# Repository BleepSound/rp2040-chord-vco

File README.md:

[![CC BY-SA 4.0][cc-by-sa-shield]][cc-by-sa]

# RP2040 VCO (Clone, made by Hagiwo)

Latest documentation available at https://bleepsound.github.io/modules/
VCO clone, originally made by HAGIWO ([link](https://note.com/solder_state/n/n64b91a171218) in japanese)

This work is licensed under a
[Creative Commons Attribution-ShareAlike 4.0 International License][cc-by-sa].

[![CC BY-SA 4.0][cc-by-sa-image]][cc-by-sa]

[cc-by-sa]: http://creativecommons.org/licenses/by-sa/4.0/
[cc-by-sa-image]: https://licensebuttons.net/l/by-sa/4.0/88x31.png
[cc-by-sa-shield]: https://img.shields.io/badge/License-CC%20BY--SA%204.0-lightgrey.svg

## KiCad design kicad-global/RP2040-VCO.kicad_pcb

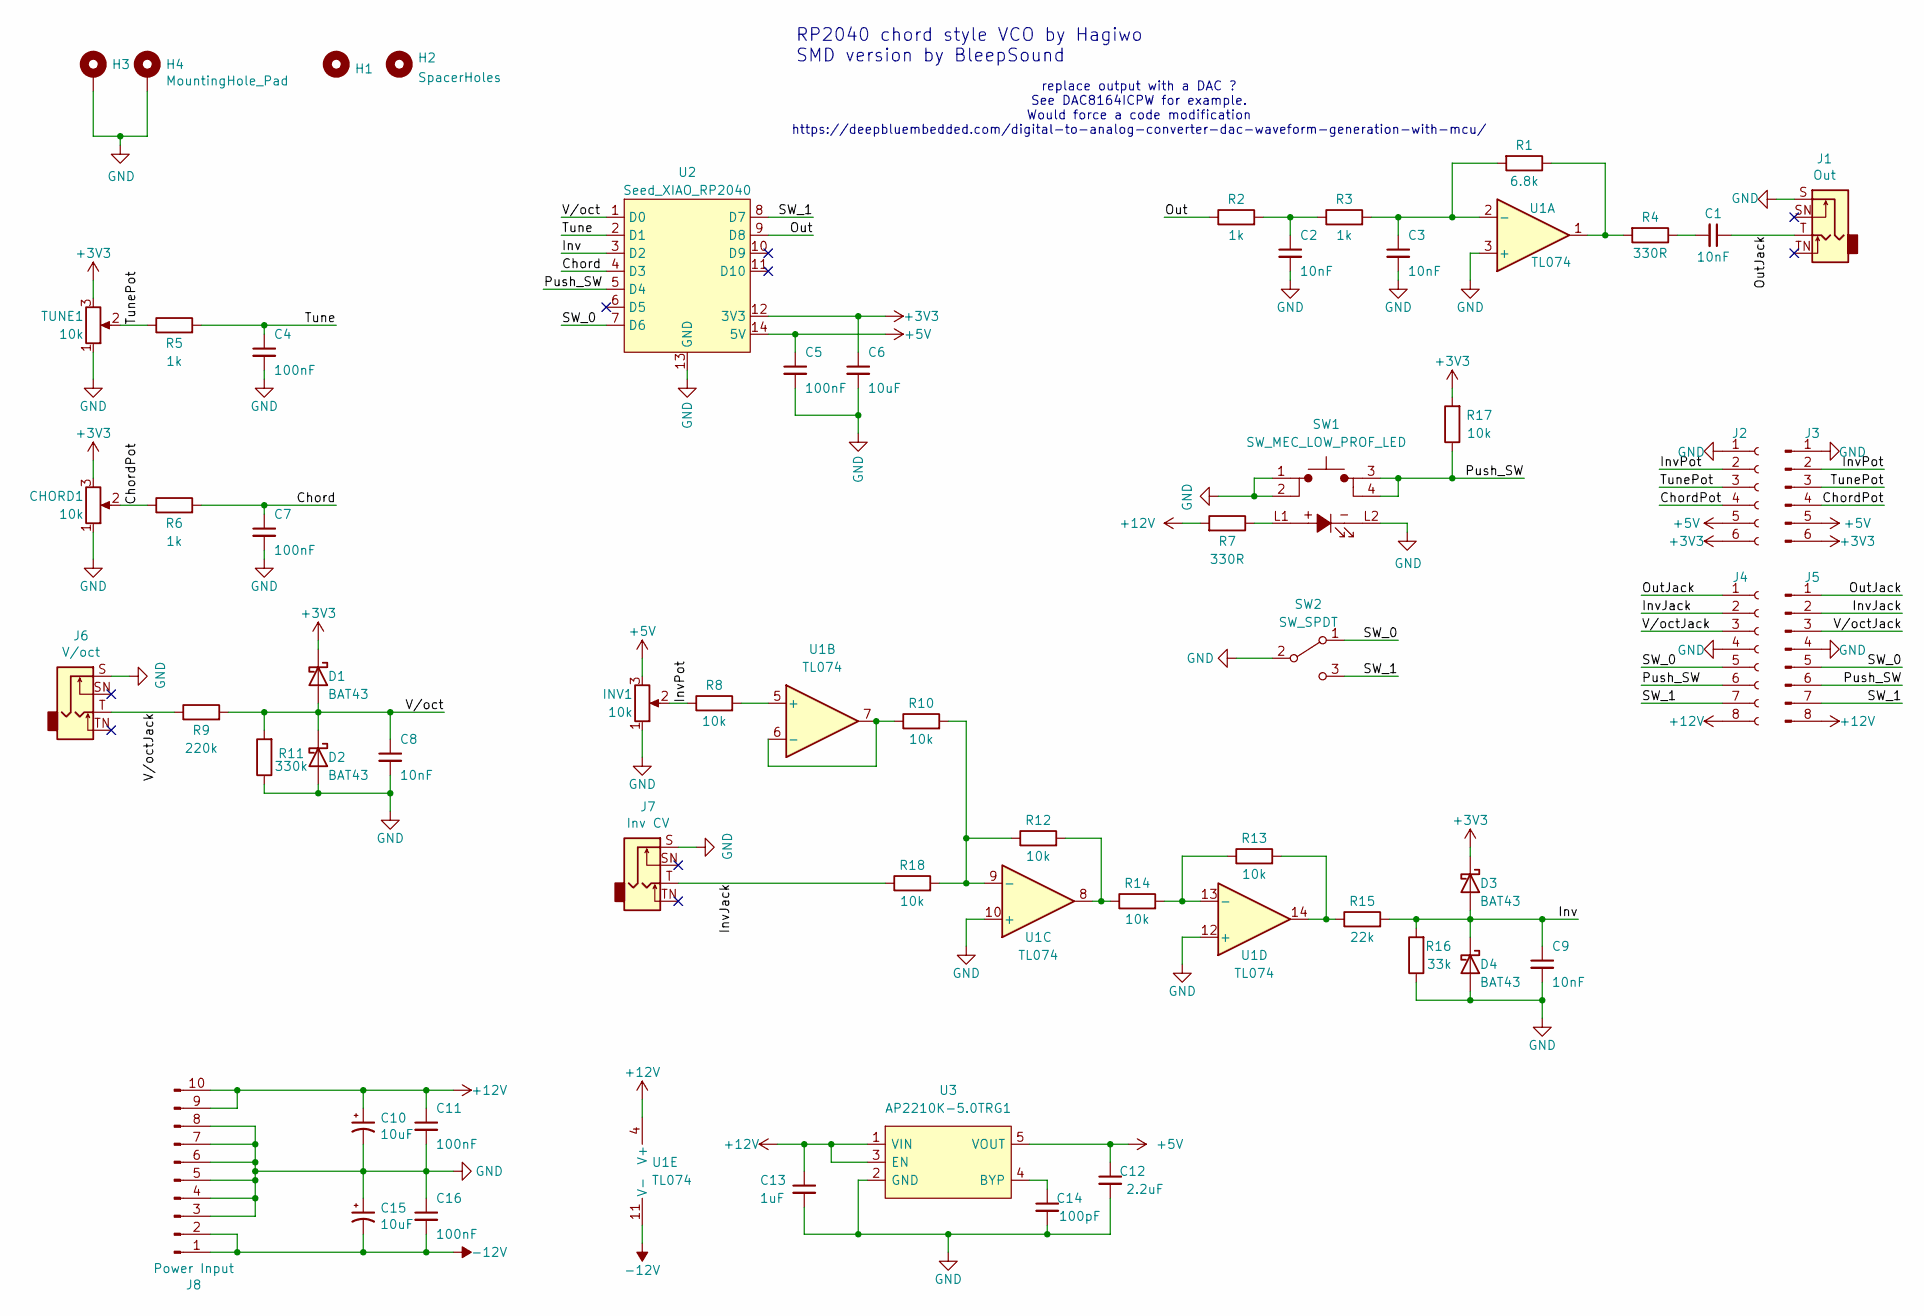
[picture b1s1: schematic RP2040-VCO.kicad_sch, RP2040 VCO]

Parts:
C1, C2, C3, C8, C9: 10nF; C_0805_2012Metric_Pad1.18x1.45mm_HandSolder
C4, C5, C7, C11, C16: 100nF; C_0805_2012Metric_Pad1.18x1.45mm_HandSolder
C6: 10uF; C_0805_2012Metric_Pad1.18x1.45mm_HandSolder
C10, C15: 10uF; CP_Elec_4x5.4
C12: 2.2uF; C_0805_2012Metric_Pad1.18x1.45mm_HandSolder
C13: 1uF; C_0805_2012Metric_Pad1.18x1.45mm_HandSolder
C14: 100pF; C_0805_2012Metric_Pad1.18x1.45mm_HandSolder
CHORD1: 10k; Pot-bourns-alpha
D1, D2, D3, D4: BAT43; D_SOD-123
H1, H2: SpacerHoles; MountingHole_3.2mm_M3
H3, H4: MountingHole_Pad; Doepfer Mounting hole
INV1: 10k; Pot-bourns-alpha
J1: Out; Thonkiconn
J2: Conn_01x06_Female; PinSocket_1x06_P2.54mm_Vertical
J3: Conn_01x06_Male; PinHeader_1x06_P2.54mm_Vertical
J4: Conn_01x08_Female; PinSocket_1x08_P2.54mm_Vertical
J5: Conn_01x08_Male; PinHeader_1x08_P2.54mm_Vertical
J6: V/oct; Thonkiconn
J7: Inv CV; Thonkiconn
J8: Power Input; IDC-Header_2x05_P2.54mm_Vertical
R1: 6.8k; R_0805_2012Metric_Pad1.20x1.40mm_HandSolder
R2, R3, R5, R6: 1k; R_0805_2012Metric_Pad1.20x1.40mm_HandSolder
R4, R7: 330R; R_0805_2012Metric_Pad1.20x1.40mm_HandSolder
R8, R10, R12, R13, R14, R17, R18: 10k; R_0805_2012Metric_Pad1.20x1.40mm_HandSolder
R9: 220k; R_0805_2012Metric_Pad1.20x1.40mm_HandSolder
R11: 330k; R_0805_2012Metric_Pad1.20x1.40mm_HandSolder
R15: 22k; R_0805_2012Metric_Pad1.20x1.40mm_HandSolder
R16: 33k; R_0805_2012Metric_Pad1.20x1.40mm_HandSolder
SW1: SW_MEC_LOW_PROF_LED; PB01-109TL
SW2: SW_SPDT; SW_Toggle_Blue_wSlots
TUNE1: 10k; Pot-bourns-alpha
U1: TL074; SOIC-14_3.9x8.7mm_P1.27mm
U2: Seed_XIAO_RP2040; Seed XIAO RP2040
U3: AP2210K-5.0TRG1; SOT95P282X130-5N

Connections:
+3V3: C6.1, CHORD1.3, D1.1 (K), D3.1 (K), J2.6, J3.6, R17.2, TUNE1.3, U2.12 (3V3)
+5V: C5.1, C12.1, INV1.3, J2.5, J3.5, U2.14 (5V), U3.5 (VOUT)
+12V: C10.1, C11.1, C13.1, J4.8, J5.8, J8.9, J8.10, R7.2, U1.4 (V+), U3.1 (VIN), U3.3 (EN)
-12V: C15.2, C16.2, J8.1, J8.2, U1.11 (V-)
/Chord: C7.1, R6.2, U2.4 (D3)
/ChordPot: CHORD1.2, J2.4, J3.4, R6.1
/Inv: C9.1, D3.2 (A), D4.1 (K), R15.2, R16.2, U2.3 (D2)
/InvJack: J4.2, J5.2, J7.T, R18.1
/InvPot: INV1.2, J2.2, J3.2, R8.1
/Out: R2.1, U2.9 (D8)
/OutJack: C1.1, J1.T, J4.1, J5.1
/Push_SW: J4.6, J5.6, R17.1, SW1.3, SW1.4, U2.5 (D4)
/SW_0: J4.5, J5.5, SW2.1 (A), U2.7 (D6)
/SW_1: J4.7, J5.7, SW2.3 (C), U2.8 (D7)
/Tune: C4.1, R5.2, U2.2 (D1)
/TunePot: J2.3, J3.3, R5.1, TUNE1.2
/V/oct: C8.1, D1.2 (A), D2.1 (K), R9.2, R11.2, U2.1 (D0)
/V/octJack: J4.3, J5.3, J6.T, R9.1
GND: C2.2, C3.2, C4.2, C5.2, C6.2, C7.2, C8.2, C9.2, C10.2, C11.2, C12.2, C13.2, C14.2, C15.1, C16.1, CHORD1.1, D2.2 (A), D4.2 (A), H3.1, H4.1, INV1.1, J1.S, J2.1, J3.1, J4.4, J5.4, J6.S, J7.S, J8.3, J8.4, J8.5, J8.6, J8.7, J8.8, R11.1, R16.1, SW1.1, SW1.2, SW1.L2, SW2.2 (B), TUNE1.1, U1.3 (+), U1.10 (+), U1.12 (+), U2.13 (GND), U3.2 (GND)
unnamed: C1.2, R4.1
unnamed: C2.1, R2.2, R3.1
unnamed: R1.1, R4.2, U1.1
unnamed: R7.1, SW1.L1
unnamed: R12.2, R14.1, U1.8
unnamed: R13.2, R15.1, U1.14
unnamed: C3.1, R1.2, R3.2, U1.2 (-)
unnamed: R8.2, U1.5 (+)
unnamed: R10.1, U1.6 (-), U1.7
unnamed: R10.2, R12.1, R18.2, U1.9 (-)
unnamed: R13.1, R14.2, U1.13 (-)
unnamed: C14.1, U3.4 (BYP)

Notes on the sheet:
replace output with a DAC ? See DAC8164ICPW for example. Would force a code modification https://deepbluembedded.com/digital-to-analog-converter-dac-waveform-generation-with-mcu/
RP2040 chord style VCO by Hagiwo SMD version by BleepSound

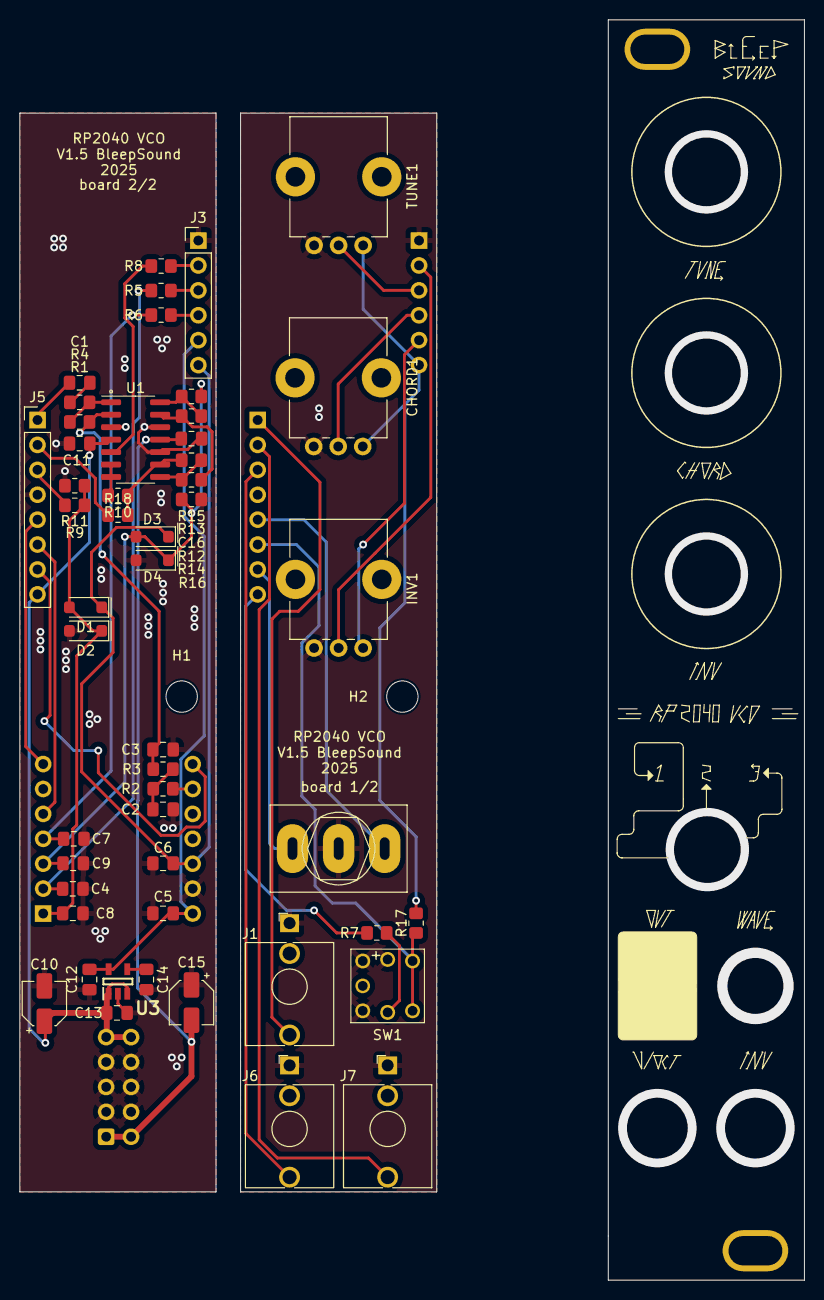
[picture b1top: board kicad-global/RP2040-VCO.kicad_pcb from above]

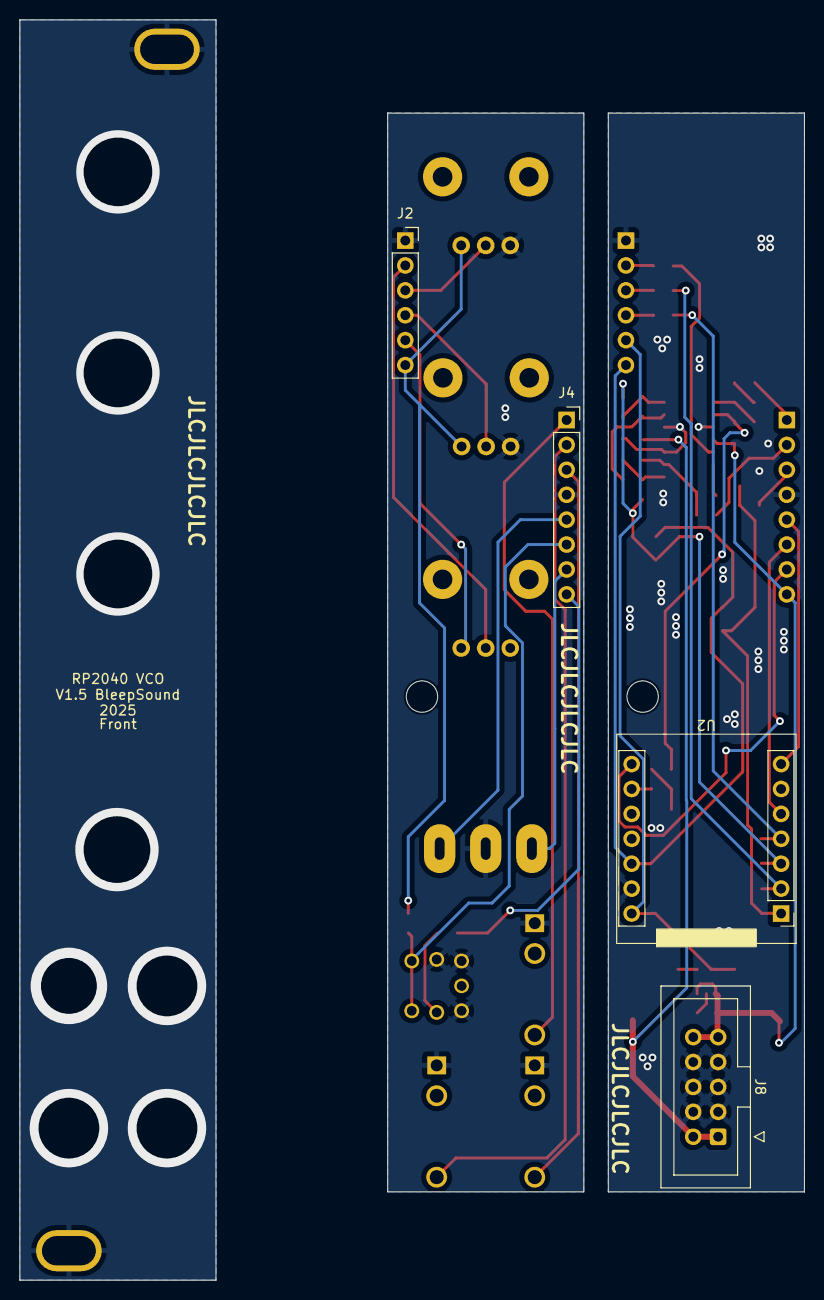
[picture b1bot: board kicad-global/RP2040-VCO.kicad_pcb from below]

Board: 2 copper layers, 80.0 x 128.5 mm, 58 parts (4 on the bottom side), 31 nets.

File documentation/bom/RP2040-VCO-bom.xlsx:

KiBot Bill of Materials
Schematic: | RP2040-VCO | Component Groups: | 29
Variant: | default | Component Count: | 53 (39 SMD/ 14 THT)
Revision: |  | Fitted Components: | 53 (39 SMD/ 14 THT)
Date: | 2023-06-10_14-17-27 | Number of PCBs: | 1
KiCad Version: | 7.0.5.1-1-g8f565ef7f0-dirty-deb11 | Total Components: | 53
Row | Description | References | Value | Footprint | Quantity Per PCB | Comment
1 | Unpolarized capacitor, small symbol | C14 | 100pF | C_0805_2012Metric_Pad1.18x1.45mm_HandSolder | 1
2 | Unpolarized capacitor, small symbol | C1 C2 C3 C8 C9 | 10nF | C_0805_2012Metric_Pad1.18x1.45mm_HandSolder | 5
3 | Unpolarized capacitor, small symbol | C4 C5 C7 C11 C16 | 100nF | C_0805_2012Metric_Pad1.18x1.45mm_HandSolder | 5
4 | Unpolarized capacitor, small symbol | C13 | 1uF | C_0805_2012Metric_Pad1.18x1.45mm_HandSolder | 1
5 | Unpolarized capacitor, small symbol | C12 | 2.2uF | C_0805_2012Metric_Pad1.18x1.45mm_HandSolder | 1
6 |  | C10 C15 | 10uF | CP_Elec_4x5.4 | 2
7 | Unpolarized capacitor, small symbol | C6 | 10uF | C_0805_2012Metric_Pad1.18x1.45mm_HandSolder | 1
8 |  | CHORD1 INV1 TUNE1 | 10k | Pot-bourns-alpha | 3
9 | 30V 0.2A Small Signal Schottky diode, SOD-123 | D1 D2 D3 D4 | BAT43 | D_SOD-123 | 4
10 | Generic connector, single row, 01x06, script generated (kicad-library-utils/sch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 | J2 | Conn_01x06_Female | PinSocket_1x06_P2.54mm_Vertical | 1
11 | Generic connector, single row, 01x06, script generated (kicad-library-utils/sch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 | J3 | Conn_01x06_Male | PinHeader_1x06_P2.54mm_Vertical | 1
12 | Generic connector, single row, 01x08, script generated (kicad-library-utils/sch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 | J4 | Conn_01x08_Female | PinSocket_1x08_P2.54mm_Vertical | 1
13 | Generic connector, single row, 01x08, script generated (kicad-library-utils/sch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 | J5 | Conn_01x08_Male | PinHeader_1x08_P2.54mm_Vertical | 1
14 | Audio Jack, 2 Poles (Mono / TS), Switched Pole (Normalling) | J1 J6 J7 | Out | Thonkiconn | 3
15 | Generic connector, single row, 01x10, script generated (kicad-library-utils/sch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 | J8 | Power Input | IDC-Header_2x05_P2.54mm_Vertical | 1
16 | Resistor | R4 | 330R | R_0805_2012Metric_Pad1.20x1.40mm_HandSolder | 1
17 | Resistor | R2 R3 R5 R6 | 1k | R_0805_2012Metric_Pad1.20x1.40mm_HandSolder | 4
18 | Resistor | R7 | 2.2k | R_0805_2012Metric_Pad1.20x1.40mm_HandSolder | 1
19 | Resistor | R1 | 6.8k | R_0805_2012Metric_Pad1.20x1.40mm_HandSolder | 1
20 | Resistor | R8 R10 R12 R13 R14 R17 | 10k | R_0805_2012Metric_Pad1.20x1.40mm_HandSolder | 6
21 | Resistor | R15 | 22k | R_0805_2012Metric_Pad1.20x1.40mm_HandSolder | 1
22 | Resistor | R16 | 33k | R_0805_2012Metric_Pad1.20x1.40mm_HandSolder | 1
23 | Resistor | R9 | 220k | R_0805_2012Metric_Pad1.20x1.40mm_HandSolder | 1
24 | Resistor | R11 | 330k | R_0805_2012Metric_Pad1.20x1.40mm_HandSolder | 1
25 | MEC Low Profile single pole normally-open illuminated tactile switch | SW1 | SW_MEC_LOW_PROF_LED | PB01-109TL | 1
26 | Switch, single pole double throw | SW2 | SW_SPDT | SW_Toggle_Blue_wSlots | 1
27 | LDO Voltage Regulators 300mA CMOS LDO 5.0V 250mV | U3 | AP2210K-5.0TRG1 | SOT95P282X130-5N | 1
28 | Microcontroler | U2 | Seed_XIAO_RP2040 | Seed XIAO RP2040 | 1
29 | Quad Low-Noise JFET-Input Operational Amplifiers, DIP-14/SOIC-14 | U1 | TL074 | SOIC-14_3.9x8.7mm_P1.27mm | 1

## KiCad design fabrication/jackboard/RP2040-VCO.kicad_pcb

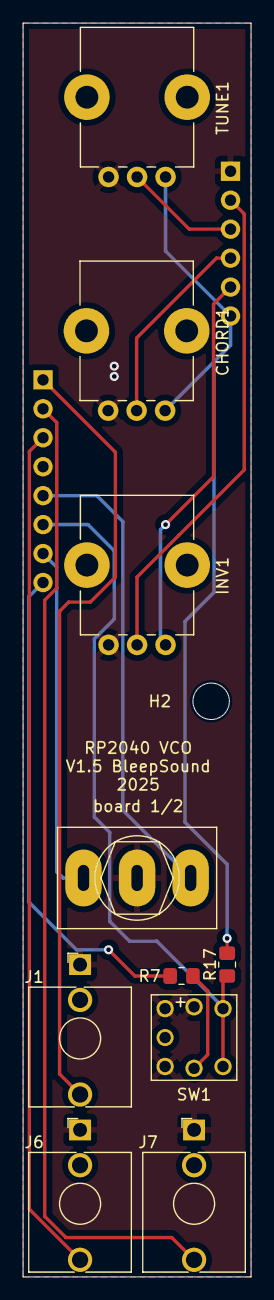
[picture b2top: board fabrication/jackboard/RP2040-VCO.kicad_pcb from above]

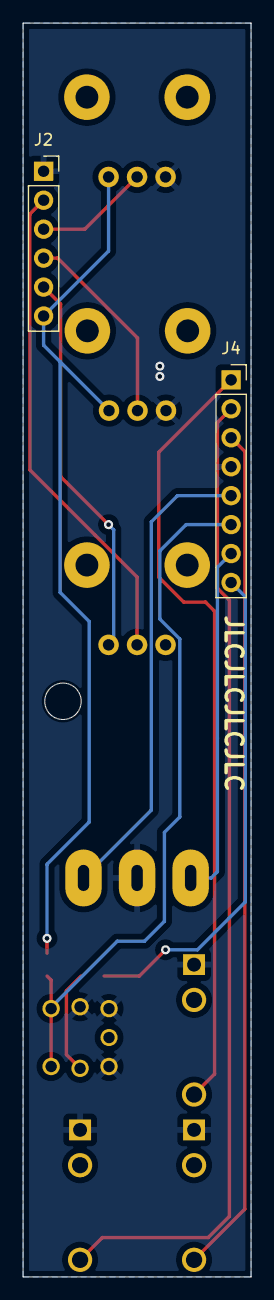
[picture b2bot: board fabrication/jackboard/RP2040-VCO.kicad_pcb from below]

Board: 2 copper layers, 20.0 x 110.0 mm, 13 parts (2 on the bottom side), 14 nets.

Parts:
CHORD1: 10k; Pot-bourns-alpha
H2: SpacerHoles; MountingHole_3.2mm_M3
INV1: 10k; Pot-bourns-alpha
J1: Out; Thonkiconn
J2: Conn_01x06_Female; PinSocket_1x06_P2.54mm_Vertical
J4: Conn_01x08_Female; PinSocket_1x08_P2.54mm_Vertical
J6: V/oct; Thonkiconn
J7: Inv CV; Thonkiconn
R7: 330R; R_0805_2012Metric_Pad1.20x1.40mm_HandSolder
R17: 10k; R_0805_2012Metric_Pad1.20x1.40mm_HandSolder
SW1: SW_MEC_LOW_PROF_LED; PB01-109TL
SW2: SW_SPDT; SW_Toggle_Blue_wSlots
TUNE1: 10k; Pot-bourns-alpha

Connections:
+3V3: CHORD1.3, J2.6, R17.2, TUNE1.3
+5V: INV1.3, J2.5
+12V: J4.8, R7.2
/ChordPot: CHORD1.2, J2.4
/InvJack: J4.2, J7.T
/InvPot: INV1.2, J2.2
/OutJack: J1.T, J4.1
/Push_SW: J4.6, R17.1, SW1.3, SW1.4
/SW_0: J4.5, SW2.1 (A)
/SW_1: J4.7, SW2.3 (C)
/TunePot: J2.3, TUNE1.2
/V/octJack: J4.3, J6.T
GND: CHORD1.1, INV1.1, J1.S, J2.1, J4.4, J6.S, J7.S, SW1.1, SW1.2, SW1.L2, SW2.2 (B), TUNE1.1
unnamed: R7.1, SW1.L1

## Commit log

2023-01-20 first commit (schem finished)
2023-01-21 finished schem and started pcb
2023-01-31 update schem + begin routing
2023-01-31 Routing finished
2023-02-18 update VCO pcb
2023-02-18 Add workflow
2023-02-18 add circuit gerber
2023-02-18 add jack BoM
2023-02-18 add main BoM and images
2023-02-18 add circuit BoM
2023-02-18 add front gerber
2023-02-18 add jack gerber
2023-04-09 update actions to work on push
2023-04-09 comment useless option
2023-04-09 update silkscreen
2023-04-09 update board with pullup on switch
2023-04-09 add soft for RP2040
2023-06-10 update label for tune (fix issue)
2023-10-11 add debounce for push button
2023-10-11 update pcb to v1.2 to fix switch issue with switch LED
2023-10-11 update fab files and repo organization
2023-10-11 fix broken link
2023-10-11 update soldering instructions
2023-10-11 fix led button footprint
2024-06-12 roll back software following issue with debounce
2024-10-26 clean up repo
2025-04-15 V1.4 update
    add extra 10k resistor on inv CV input (missing)
    Update BoM for clarity
2025-04-15 New gerbers for v1.4
    forgotten in previous commit
2025-10-29 v1.5
    reverse pots following issue raised on github
2025-11-27 add licence
